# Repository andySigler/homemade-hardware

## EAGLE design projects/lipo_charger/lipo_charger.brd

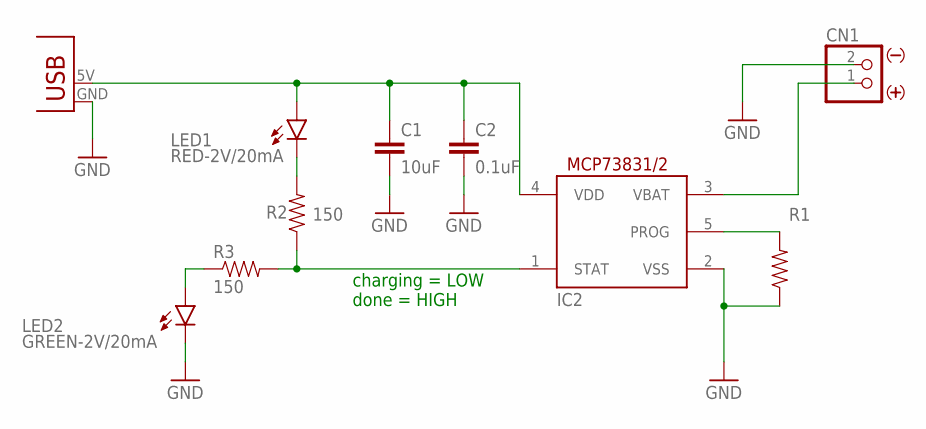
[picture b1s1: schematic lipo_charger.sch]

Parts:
C1: 10uF; 0805
C2: 0.1uF; 0805
CN1: JST_2PIN_BATTERY-SMT-HORIZ; JST-PH-2-SMT-RA
IC2: LIPO_CHARGER/OT; SOT23-5L
LED1: RED-2V/20mA; CHIP-LED0805
LED2: GREEN-2V/20mA; CHIP-LED0805
R1: 10k; 0805
R2, R3: 150; 0805
U$2: USB-PCB-POWER; USB-A-PCB-POWER

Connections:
5V: C1.1, C2.1, IC2.4 (VDD), LED1.A, U$2.5V (VBUS)
BATTERY: CN1.1 (2), IC2.3 (VBAT)
CURRENT-CONTROL: IC2.5 (PROG), R1.2
GND: C1.2, C2.2, CN1.2 (1), IC2.2 (VSS), LED2.C, R1.1, U$2.GND
unnamed: LED1.C, R2.2
unnamed: LED2.A, R3.1
STATUS: IC2.1 (STAT), R2.1, R3.2

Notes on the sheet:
charging = LOW done = HIGH

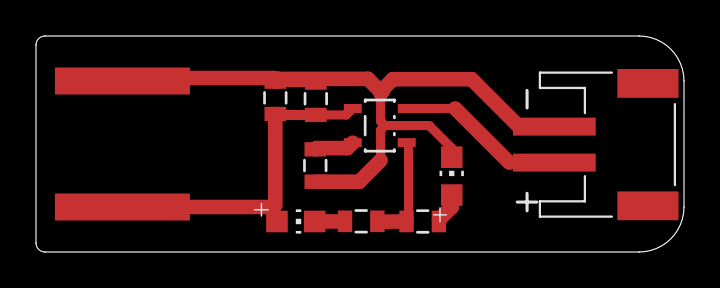
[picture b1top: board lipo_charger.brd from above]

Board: 2 copper layers, 36.0 x 12.0 mm, 10 parts (0 on the bottom side), 7 nets.

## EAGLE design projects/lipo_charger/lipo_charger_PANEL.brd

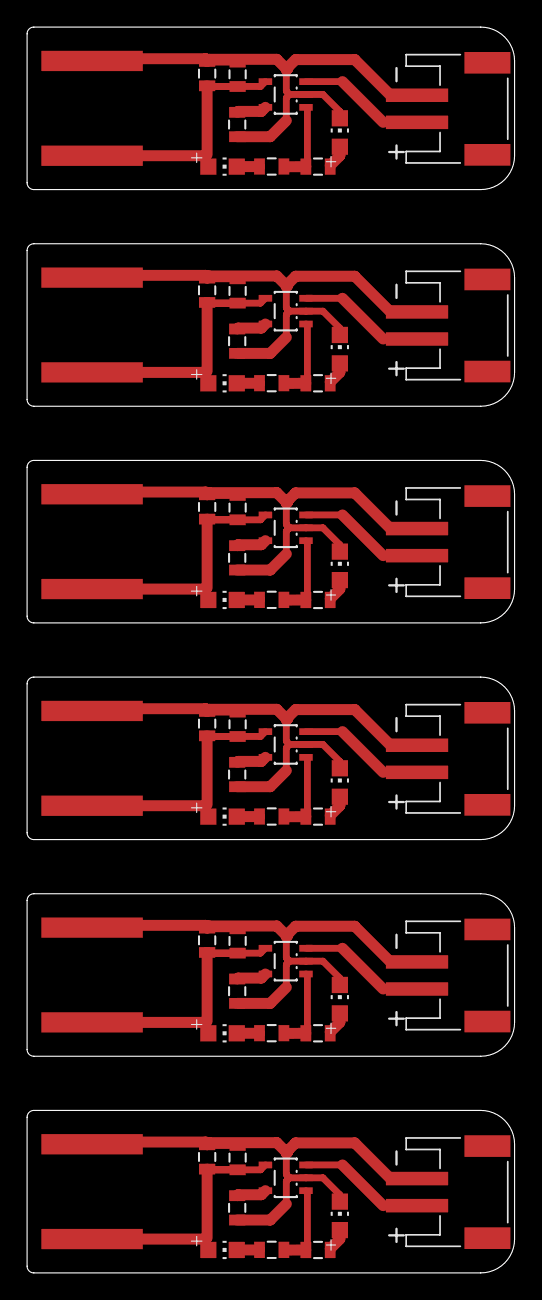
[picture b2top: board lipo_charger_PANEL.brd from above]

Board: 2 copper layers, 36.0 x 92.0 mm, 60 parts (0 on the bottom side), 42 nets.

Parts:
C1, C3, C5, C7, C9, C11: 10uF; 0805
C2, C4, C6, C8, C10, C12: 0.1uF; 0805
CN1, CN2, CN3, CN4, CN5, CN6: JST-PH-2-SMT-RA
IC1, IC2, IC3, IC4, IC5, IC6: LIPO_CHARGER/OT; SOT23-5L
LED1, LED3, LED5, LED7, LED9, LED11: RED-2V/20mA; CHIP-LED0805
LED2, LED4, LED6, LED8, LED10, LED12: GREEN-2V/20mA; CHIP-LED0805
R1, R6, R9, R12, R15, R18: 10k; 0805
R2, R3, R4, R5, R7, R8, R10, R11, R13, R14, R16, R17: 150; 0805
U$1, U$2, U$3, U$4, U$5, U$6: USB-PCB-POWER; USB-A-PCB-POWER

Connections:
5V: C1.1, C2.1, IC2.4, LED1.A, U$2.5V
5V1: C3.1, C4.1, IC1.4, LED3.A, U$1.5V
5V2: C5.1, C6.1, IC3.4, LED5.A, U$3.5V
5V3: C7.1, C8.1, IC4.4, LED7.A, U$4.5V
5V4: C9.1, C10.1, IC5.4, LED9.A, U$5.5V
5V5: C11.1, C12.1, IC6.4, LED11.A, U$6.5V
BATTERY: CN1.1, IC2.3
BATTERY1: CN2.1, IC1.3
BATTERY2: CN3.1, IC3.3
BATTERY3: CN4.1, IC4.3
BATTERY4: CN5.1, IC5.3
BATTERY5: CN6.1, IC6.3
CURRENT-CONTROL: IC2.5, R1.2
CURRENT-CONTROL1: IC1.5, R6.2
CURRENT-CONTROL2: IC3.5, R9.2
CURRENT-CONTROL3: IC4.5, R12.2
CURRENT-CONTROL4: IC5.5, R15.2
CURRENT-CONTROL5: IC6.5, R18.2
GND: C1.2, C2.2, CN1.2, IC2.2, LED2.C, R1.1, U$2.GND
GND1: C3.2, C4.2, CN2.2, IC1.2, LED4.C, R6.1, U$1.GND
GND2: C5.2, C6.2, CN3.2, IC3.2, LED6.C, R9.1, U$3.GND
GND3: C7.2, C8.2, CN4.2, IC4.2, LED8.C, R12.1, U$4.GND
GND4: C9.2, C10.2, CN5.2, IC5.2, LED10.C, R15.1, U$5.GND
GND5: C11.2, C12.2, CN6.2, IC6.2, LED12.C, R18.1, U$6.GND
unnamed: LED3.C, R5.2
unnamed: LED1.C, R2.2
unnamed: LED2.A, R3.1
unnamed: LED4.A, R4.1
unnamed: LED5.C, R8.2
unnamed: LED6.A, R7.1
unnamed: LED7.C, R11.2
unnamed: LED8.A, R10.1
unnamed: LED9.C, R14.2
unnamed: LED10.A, R13.1
unnamed: LED11.C, R17.2
unnamed: LED12.A, R16.1
STATUS: IC2.1, R2.1, R3.2
STATUS1: IC1.1, R4.2, R5.1
STATUS2: IC3.1, R7.2, R8.1
STATUS3: IC4.1, R10.2, R11.1
STATUS4: IC5.1, R13.2, R14.1
STATUS5: IC6.1, R16.2, R17.1

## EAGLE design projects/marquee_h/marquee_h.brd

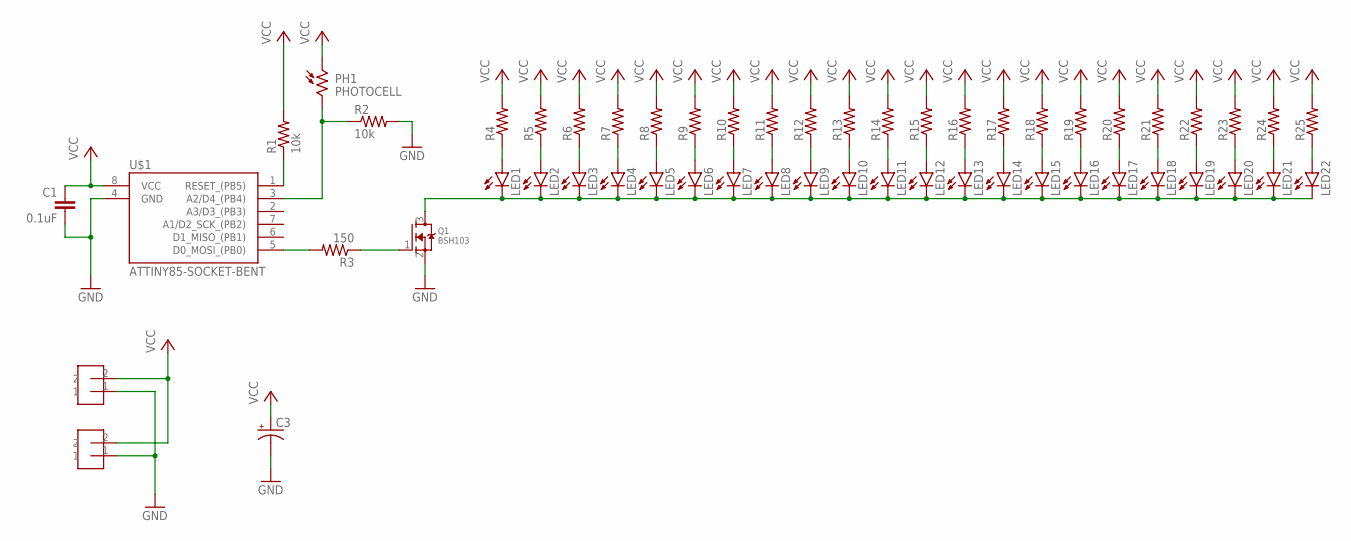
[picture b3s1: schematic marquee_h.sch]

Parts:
C1: 0.1uF; 0805
C3: CAP_POLD; PANASONIC_D
LED1, LED2, LED3, LED4, LED5, LED6, LED7, LED8, LED9, LED10, LED11, LED12, LED13, LED14, LED15, LED16, LED17, LED18, LED19, LED20, LED21, LED22: LED0603; LED-0603
PH1: PHOTOCELL; PHOTOCELL_ADAFRUIT
Q1: BSH103; SOT23
R1, R2: 10k; 0805
R3: 150; 0805
R4, R5, R6, R7, R8, R9, R10, R11, R12, R13, R14, R15, R16, R17, R18, R19, R20, R21, R22, R23, R24, R25: RESISTOR0603; 0603-RES
U$1: ATTINY85-SOCKET-BENT; SOCKET-8PIN-BENT
U$2, U$3: HEADER-2

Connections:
GND: C1.2, C3.-, Q1.2 (S), R2.2, U$1.4 (GND), U$2.1, U$3.1
GND_LED: LED1.C, LED2.C, LED3.C, LED4.C, LED5.C, LED6.C, LED7.C, LED8.C, LED9.C, LED10.C, LED11.C, LED12.C, LED13.C, LED14.C, LED15.C, LED16.C, LED17.C, LED18.C, LED19.C, LED20.C, LED21.C, LED22.C, Q1.3 (D)
unnamed: LED1.A, R4.1
unnamed: R3.2, U$1.5 (D0_MOSI_(PB0))
unnamed: Q1.1 (G), R3.1
unnamed: LED2.A, R5.1
unnamed: LED3.A, R6.1
unnamed: LED4.A, R7.1
unnamed: LED5.A, R8.1
unnamed: LED6.A, R9.1
unnamed: LED7.A, R10.1
unnamed: LED8.A, R11.1
unnamed: LED9.A, R12.1
unnamed: LED10.A, R13.1
unnamed: LED11.A, R14.1
unnamed: LED12.A, R15.1
unnamed: LED13.A, R16.1
unnamed: LED14.A, R17.1
unnamed: LED15.A, R18.1
unnamed: LED16.A, R19.1
unnamed: LED17.A, R20.1
unnamed: LED18.A, R21.1
unnamed: LED19.A, R22.1
unnamed: LED20.A, R23.1
unnamed: LED21.A, R24.1
unnamed: LED22.A, R25.1
RESET: R1.1, U$1.1 (RESET_(PB5))
SENSOR: PH1.2, R2.1, U$1.3 (A2/D4_(PB4))
VCC: C1.1, C3.+, PH1.1, R1.2, R4.2, R5.2, R6.2, R7.2, R8.2, R9.2, R10.2, R11.2, R12.2, R13.2, R14.2, R15.2, R16.2, R17.2, R18.2, R19.2, R20.2, R21.2, R22.2, R23.2, R24.2, R25.2, U$1.8 (VCC), U$2.2, U$3.2

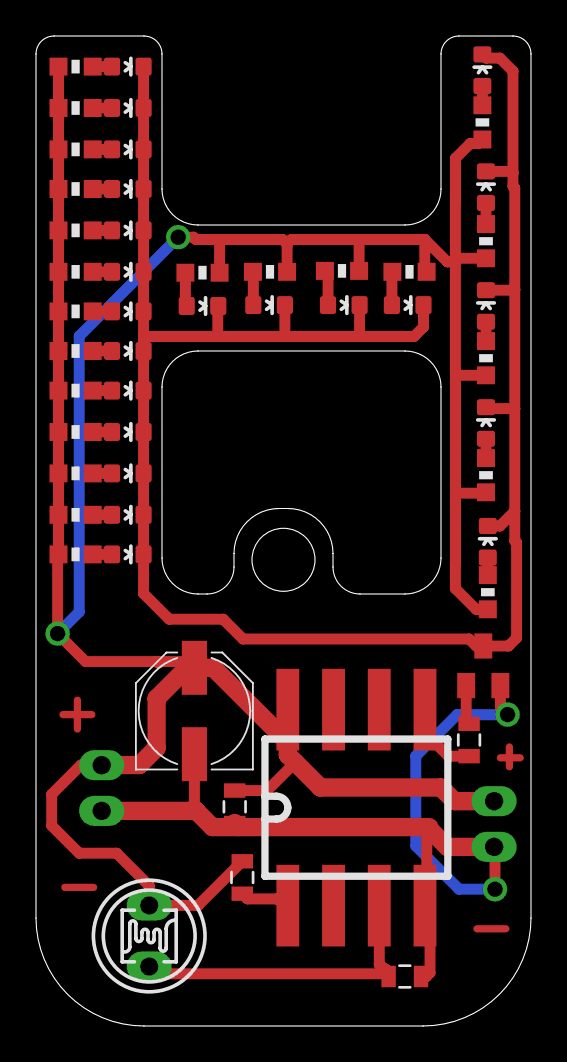
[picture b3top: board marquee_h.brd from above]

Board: 2 copper layers, 27.5 x 55.0 mm, 54 parts (0 on the bottom side), 29 nets.

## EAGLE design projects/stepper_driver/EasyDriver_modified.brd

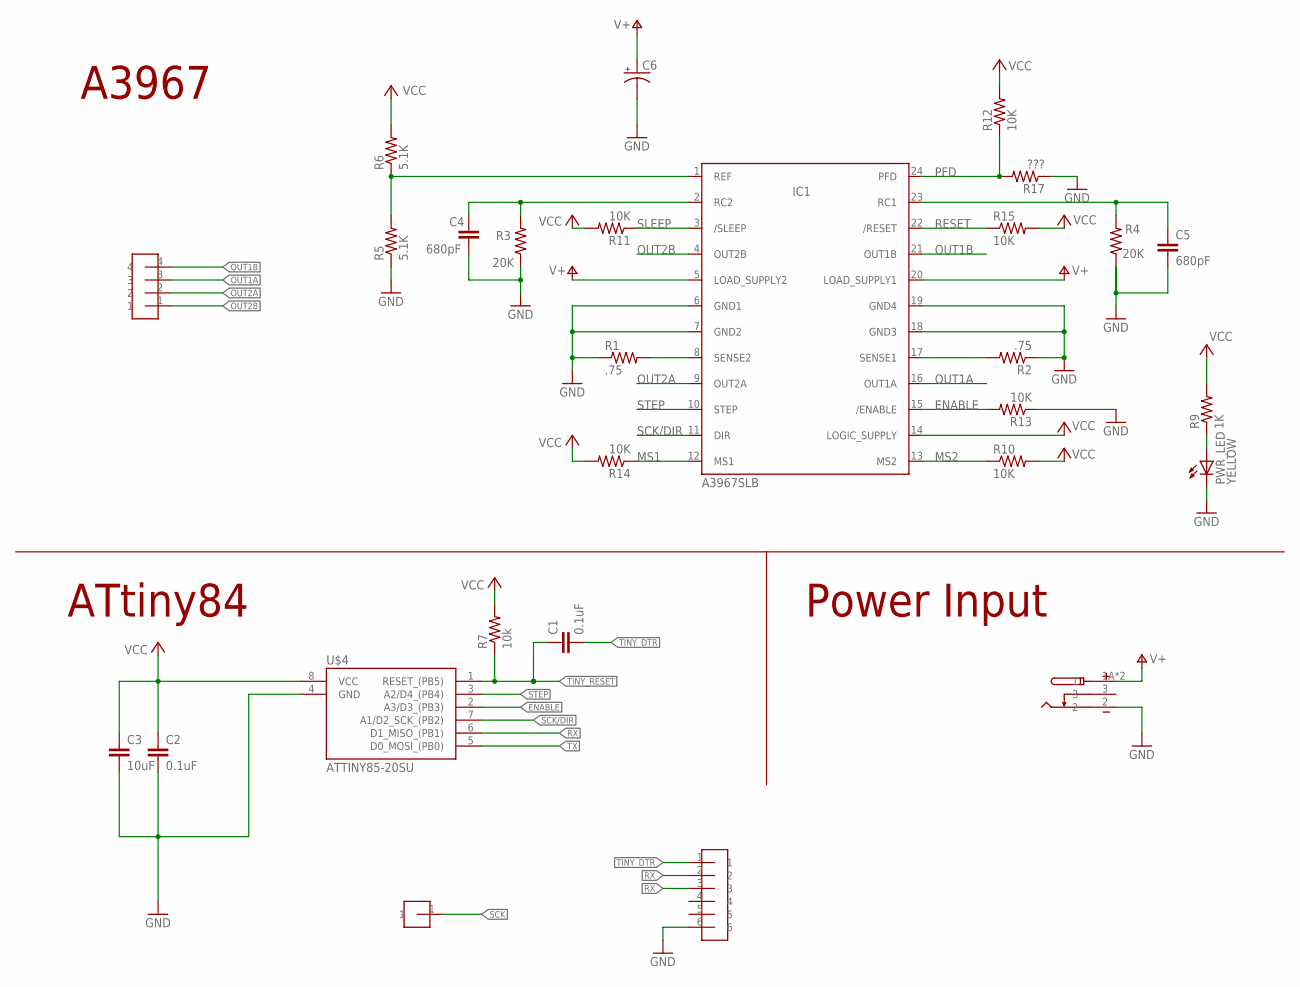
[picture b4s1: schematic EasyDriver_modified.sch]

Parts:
C1, C2: 0.1uF; 0603-CAP
C3: 10uF; 0603-CAP
C4, C5: 680pF; C0402
C6: CAP_POLG; PANASONIC_G
IC1: A3967SLB; SO24W
PWR_LED: YELLOW; LED-0603
R1, R2: .75; R0805
R3, R4: 20K; C0402
R5, R6: 5.1K; C0402
R7: 10k; 0603-RES
R9: 1K; C0402
R10, R11, R12, R13, R14, R15: 10K; C0402
R17: ???; C0402
U$1: HEADER-6
U$2: DC-BARREL-CONN-SMD; 694106106102
U$3: HEADER-1-TESTPOINT; TESTPOINT-1
U$4: ATTINY85-20SU; SOIC8
U$5: HEADER-4

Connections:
+5V: C2.1, C3.1, R7.2, U$4.8 (VCC)
ENABLE: IC1.15 (/ENABLE), R13.2, U$4.2 (A3/D3_(PB3))
GND: C2.2, C3.2, C4.2, C5.2, C6.-, IC1.6 (GND1), IC1.7 (GND2), IC1.18 (GND3), IC1.19 (GND4), PWR_LED.C, R1.1, R2.1, R3.1, R4.1, R5.1, R13.1, R17.1, U$1.6, U$2.2, U$4.4 (GND)
MS1: IC1.12 (MS1), R14.1
MS2: IC1.13 (MS2), R10.1
unnamed: IC1.8 (SENSE2), R1.2
unnamed: PWR_LED.A, R9.1
unnamed: IC1.17 (SENSE1), R2.2
unnamed: C4.1, IC1.2 (RC2), R3.2
unnamed: C5.1, IC1.23 (RC1), R4.2
unnamed: IC1.1 (REF), R5.2, R6.1
OUT1A: IC1.16 (OUT1A), U$5.3
OUT1B: IC1.21 (OUT1B), U$5.4
OUT2A: IC1.9 (OUT2A), U$5.2
OUT2B: IC1.4 (OUT2B), U$5.1
PFD: IC1.24 (PFD), R12.1, R17.2
RESET: IC1.22 (/RESET), R15.1
RX: U$1.2, U$1.3, U$4.6 (D1_MISO_(PB1))
SCK: U$3.1
SCK/DIR: IC1.11 (DIR), U$4.7 (A1/D2_SCK_(PB2))
SLEEP: IC1.3 (/SLEEP), R11.1
STEP: IC1.10 (STEP), U$4.3 (A2/D4_(PB4))
TINY_DTR: C1.2, U$1.1
TINY_RESET: C1.1, R7.1, U$4.1 (RESET_(PB5))
TX: U$4.5 (D0_MOSI_(PB0))
V+: C6.+, IC1.5 (LOAD_SUPPLY2), IC1.20 (LOAD_SUPPLY1), U$2.1A (1), U$2.1B (1)
VCC: IC1.14 (LOGIC_SUPPLY), R6.2, R9.2, R10.2, R11.2, R12.2, R14.2, R15.2

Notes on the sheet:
A3967
ATtiny84
Power Input

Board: 2 copper layers, 28 parts (0 on the bottom side), 25 nets, no tracks yet.

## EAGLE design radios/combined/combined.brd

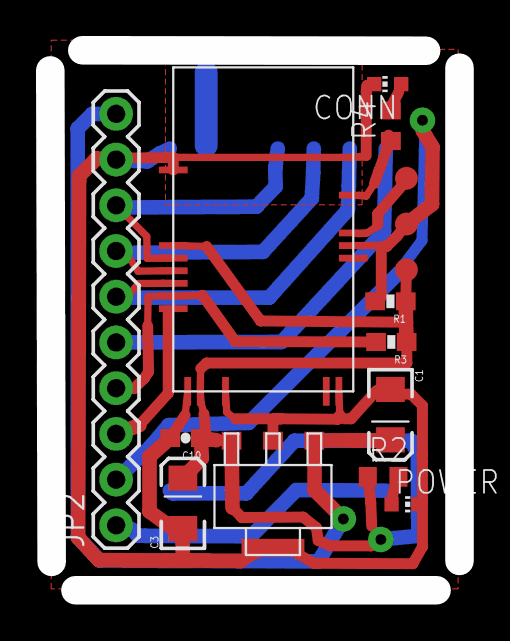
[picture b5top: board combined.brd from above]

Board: 2 copper layers, 22.7 x 30.0 mm, 16 parts (1 on the bottom side), 15 nets.

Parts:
C1, C3: 10uF; EIA3216
C10: 1uF; 0603-CAP
CLOCK, CLOCK1: PAD; SMD-ROUND
CONN: CHIP-LED0603
JP2: M10"; 1X10
POWER: CHIP-LED0603
R1, R3: 10k; 0603-RES
R2, R4: 10k; R0603
U$1: RFM69; S0C-RFM69
U$3: REGULATOR3.3V-UA78M33CDCYR; SOT223
U$5: NRF51-MDBT40-SPI; SOC-NRF51-MDBT40-SPI
VCC: PAD; SMD-ROUND

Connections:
BT-REQ: JP2.3, U$5.P0.25
BT-SS: JP2.4, R3.2, U$5.P0.24
GND: C1.C, C3.C, C10.2, CONN.C, JP2.9, POWER.C, U$1.GND, U$3.2, U$3.4, U$5.GND1, U$5.GND2, U$5.GND3, U$5.GND4, U$5.GND5, U$5.P0.30
MISO: JP2.7, U$1.MISO, U$5.P0.22
MOSI: JP2.6, U$1.MOSI, U$5.P0.23
unnamed: POWER.A, R2.2
unnamed: R4.1, U$5.P0.19
unnamed: CONN.A, R4.2
unnamed: CLOCK.P$1, U$5.SWCLK
RF-REQ: JP2.1, U$1.REQ
RF-SS: JP2.5, U$1.SS
SCK: JP2.8, U$1.SCK, U$5.P0.21
SWDIO/RST: CLOCK1.P$1, JP2.2, R1.2, U$5.SWDIO
VCC: C3.A, C10.1, R1.1, R2.1, R3.1, U$1.3.3V, U$3.3, U$5.AVDD, U$5.VDD, VCC.P$1
VIN: C1.A, JP2.10, U$3.1

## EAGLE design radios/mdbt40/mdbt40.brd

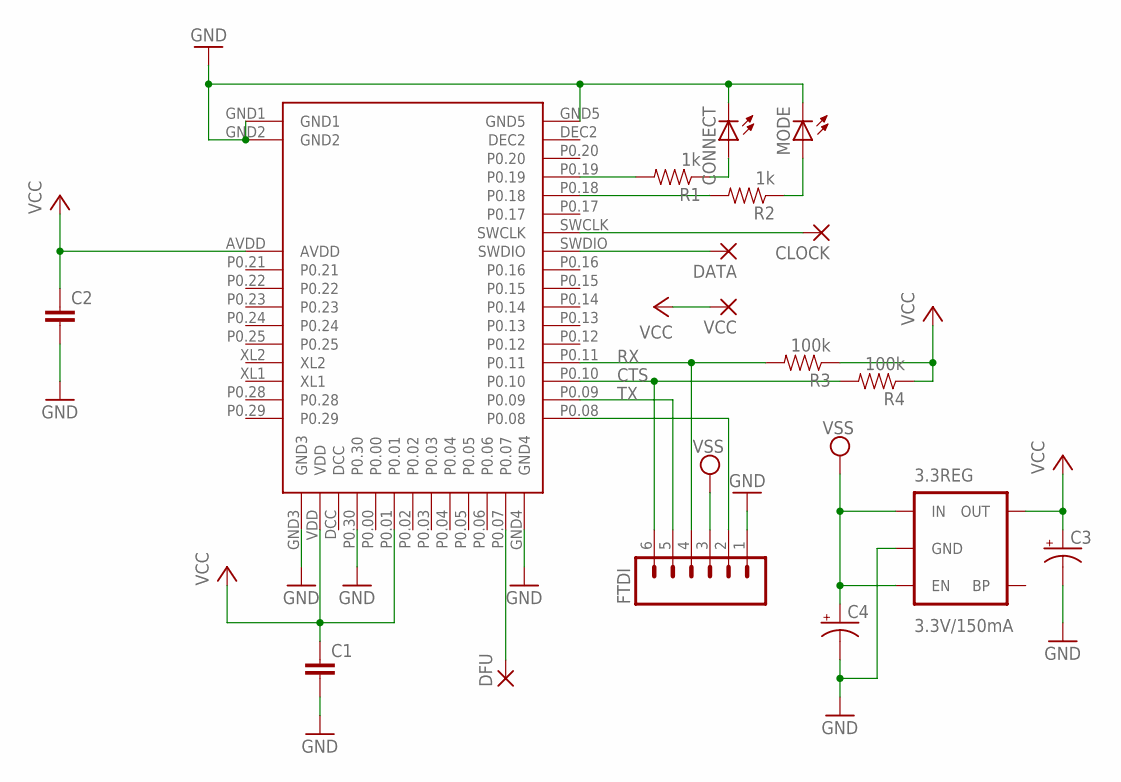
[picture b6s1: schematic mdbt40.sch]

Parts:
3.3REG: 3.3V/150mA; SOT23-5
C1, C2: CAP0603-CAP; 0603-CAP
C3, C4: CAP_POL1206; EIA3216
CLOCK: SMD2; SMD1,27-2,54
CONNECT: LEDCHIPLED_0603; CHIPLED_0603
DATA: SMD2; SMD1,27-2,54
DFU: SMD2; SMD1,27-2,54
FTDI: M06LONGPADS; 1X06_LONGPADS
MODE: LEDCHIPLED_0603; CHIPLED_0603
R1, R2: 1k; 0603-RES
R3, R4: 100k; 0603-RES
U$1: MDBT40
VCC: SMD2; SMD1,27-2,54

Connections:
CTS: FTDI.6, R4.2, U$1.P0.10
GND: 3.3REG.2 (GND), C1.2, C2.2, C3.C (-), C4.C (-), CONNECT.C, FTDI.1, MODE.C, U$1.GND1, U$1.GND2, U$1.GND3, U$1.GND4, U$1.GND5, U$1.P0.30
unnamed: R1.2, U$1.P0.19
unnamed: R2.2, U$1.P0.18
unnamed: CONNECT.A, R1.1
unnamed: MODE.A, R2.1
unnamed: CLOCK.1, U$1.SWCLK
unnamed: DATA.1, U$1.SWDIO
unnamed: DFU.1, U$1.P0.07
unnamed: FTDI.2, U$1.P0.08
RX: FTDI.4, R3.2, U$1.P0.11
TX: FTDI.5, U$1.P0.09
VCC: 3.3REG.5 (OUT), C1.1, C2.1, C3.A (+), R3.1, R4.1, U$1.AVDD, U$1.P0.01, U$1.VDD, VCC.1
VSS: 3.3REG.1 (IN), 3.3REG.3 (EN), C4.A (+), FTDI.3

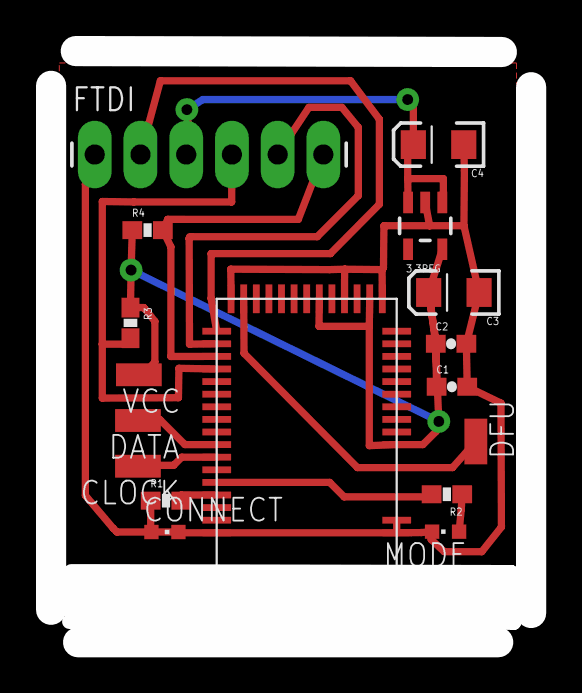
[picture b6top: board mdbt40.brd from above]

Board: 2 copper layers, 26.7 x 32.8 mm, 17 parts (0 on the bottom side), 14 nets.

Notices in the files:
parts and their libraries:
SparkFun-Aesthetics: Licensing: Creative Commons ShareAlike 4.0 International - https://creativecommons.org/licenses/by-sa/4.0
